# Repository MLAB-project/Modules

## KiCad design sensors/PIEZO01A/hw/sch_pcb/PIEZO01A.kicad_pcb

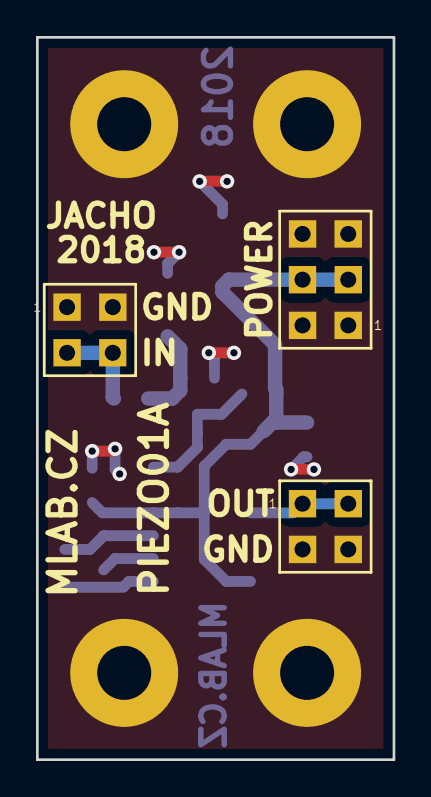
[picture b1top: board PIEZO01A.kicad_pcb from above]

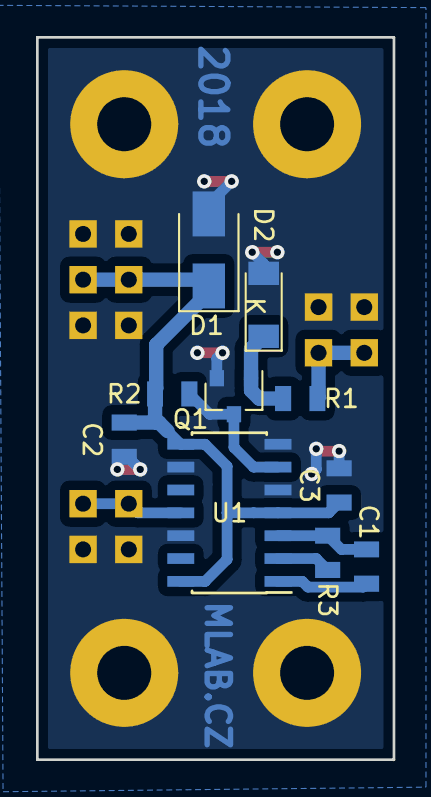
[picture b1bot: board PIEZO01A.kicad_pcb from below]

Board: 2 copper layers, 19.8 x 40.1 mm, 17 parts (10 on the bottom side), 9 nets.

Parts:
C1, C2, C3: 100nF; SMD-0805
D1: M4; Diode-SMA_Standard
D2: 1N4148; Diode-MiniMELF_Standard
J1: 5V; Straight_2x03
J2, J3: HEADER_2x02_PARALLEL; Straight_2x02
M1, M2, M3, M4: HOLE; MountingHole_3mm
Q1: BC817-40; SOT-23
R1: 1k; SMD-0805
R2: 150k; SMD-0805
R3: 10k; SMD-0805
U1: HEF4047BT.652; SOIC-14_3.9x8.7mm_P1.27mm

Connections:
+5V: C2.1, C3.1, D1.1, J1.3, J1.4, R2.2, U1.4, U1.8, U1.14
GND: C2.2, C3.2, D1.2, D2.2, J1.1, J1.2, J1.5, J1.6, J2.1, J2.2, J3.3, J3.4, M1.1, M2.1, M3.1, M4.1, Q1.2, U1.5, U1.7, U1.9, U1.12
unnamed: C1.1, U1.1
unnamed: C1.2, R3.2, U1.3
unnamed: D2.1, Q1.1, R1.1
unnamed: J2.3, J2.4, R1.2
unnamed: J3.1, J3.2, U1.11
unnamed: Q1.3, R2.1, U1.6
unnamed: R3.1, U1.2

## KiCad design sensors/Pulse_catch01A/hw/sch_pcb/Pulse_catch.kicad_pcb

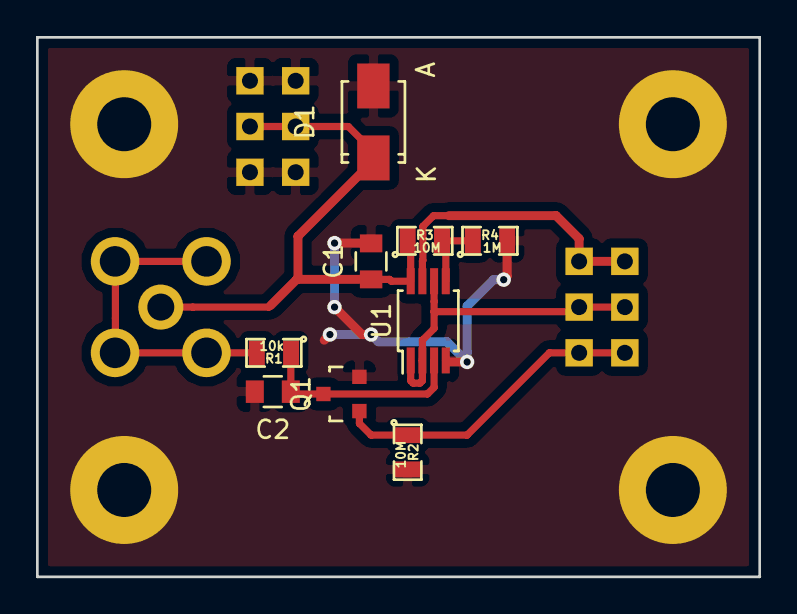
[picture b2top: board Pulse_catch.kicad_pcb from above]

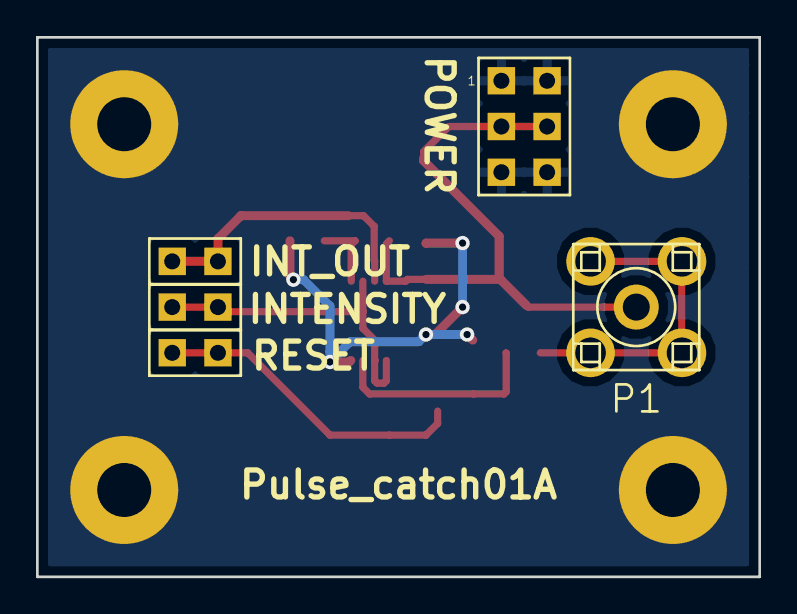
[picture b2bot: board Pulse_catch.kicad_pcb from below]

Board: 2 copper layers, 40.1 x 30.0 mm, 18 parts (5 on the bottom side), 8 nets.

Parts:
C1, C2: 100nF; C_0805
D1: D_Schottky; SMA_Standard
J1: HEADER_2x03_PARALLEL; Straight_2x03
J2: INTENSITY; Straight_2x01
J3: RESET; Straight_2x01
J4: INT_OUT; Straight_2x01
M1, M2, M3, M4: HOLE; MountingHole_3mm
P1: SMA; SMA6251A13G50
Q1: 2N7002; SOT-23
R1: 10k; SMD-0805
R2, R3: 10M; SMD-0805
R4: 1M; SMD-0805
U1: MCP6002; MSOP-8_3x3mm_Pitch0.65mm

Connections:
GNDA: C1.2, C2.2, D1.2, J1.1, J1.2, J1.5, J1.6, M1.1, M2.1, M3.1, M4.1, Q1.2, R2.2, R4.2, U1.4
unnamed: C2.1, Q1.3, R1.1, U1.3
unnamed: J2.1, J2.2, U1.1, U1.2, U1.6
unnamed: J3.1, J3.2, Q1.1, R2.1
unnamed: J4.1, J4.2, U1.7
unnamed: P1.2, R1.2
unnamed: R3.2, R4.1, U1.5
VDD: C1.1, D1.1, J1.3, J1.4, P1.1, R3.1, U1.8

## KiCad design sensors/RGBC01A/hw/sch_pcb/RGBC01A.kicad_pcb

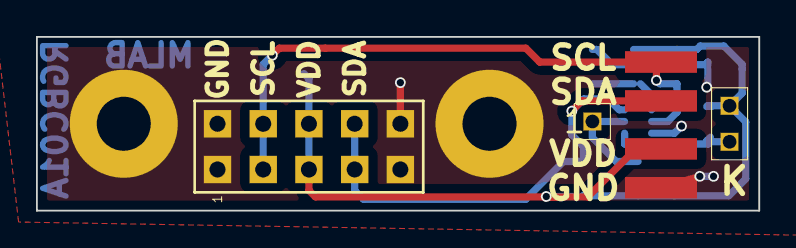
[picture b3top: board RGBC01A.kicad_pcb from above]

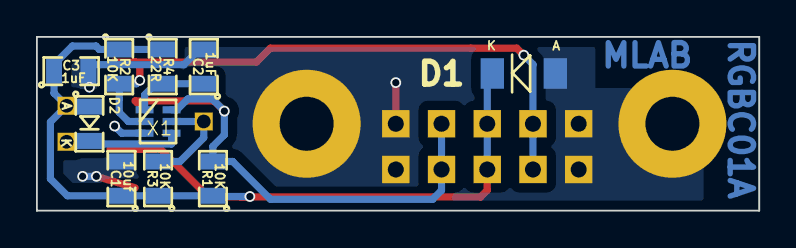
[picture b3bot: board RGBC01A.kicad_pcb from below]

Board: 2 copper layers, 40.1 x 9.7 mm, 19 parts (12 on the bottom side), 7 nets.

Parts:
C1: 10uf; SMD-0805
C2, C3: 1uF; SMD-0805
D1: BZV55C-3,6V; Diode-MiniMELF_Standard
D2: LL-S170IRC-2A; LED_0805
J1: JUMP_5X2; Straight_2x05
J2: CONN1_1; Straight_1x01
J3: CONN1_2; Straight_2x01
J4, J5, J6, J7: CONN1_1; SMD_1x1
M1, M2: HOLE; MountingHole_3mm
R1, R2, R3: 10K; SMD-0805
R4: 22R; SMD-0805
X1: TCS37717; FN

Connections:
/SCL: J1.3, J1.4, J5.1, R2.2, X1.2
/SDA: J1.7, J1.8, J6.1, R1.2, X1.6
GND: C1.2, C2.2, C3.2, D1.1, J1.1, J1.2, J1.9, J1.10, J7.1, M1.1, M2.1, X1.3
unnamed: C2.1, R4.2, X1.1
unnamed: D2.2, J3.2, X1.4
unnamed: J2.1, R3.2, X1.5
VDD: C1.1, C3.1, D1.2, D2.1, J1.5, J1.6, J3.1, J4.1, R1.1, R2.1, R3.1, R4.1

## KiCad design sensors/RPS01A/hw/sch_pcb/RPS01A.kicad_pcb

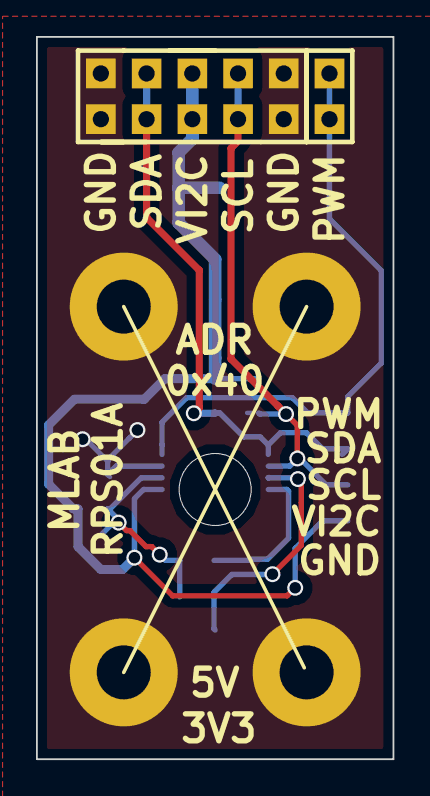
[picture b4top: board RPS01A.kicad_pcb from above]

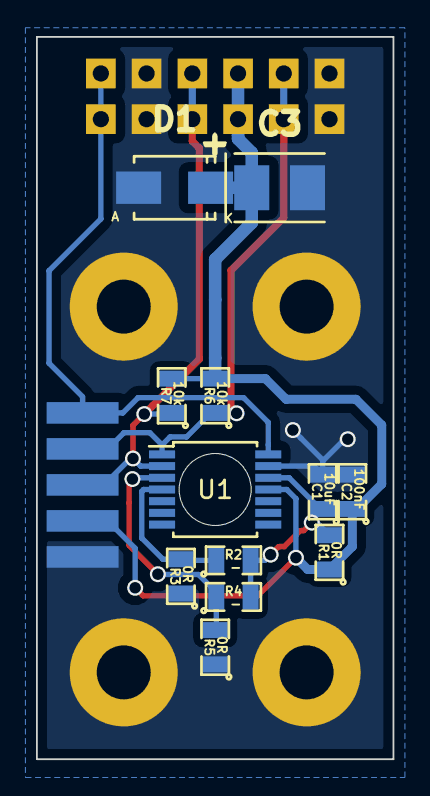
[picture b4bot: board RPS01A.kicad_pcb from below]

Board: 2 copper layers, 19.8 x 40.1 mm, 19 parts (13 on the bottom side), 8 nets.

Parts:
C1: 10uF; SMD-0805
C2: 100nF; SMD-0805
C3: 10uF; TantalC_SizeB_Reflow
D1: M4; SMA_Standard
J1: JUMP_5X2; Pin_Header_Straight_2x05
J2: JUMP_2x1; Pin_Header_Straight_2x01
J3: JUMP_5X2; SMD_JUMP1X5
P1, P2, P3, P4: _; MountingHole_3mm
R1, R3, R5: 0R; SMD-0805
R2, R4: -; SMD-0805
R6, R7: 10k; SMD-0805
U1: AS5048B; TSSOP-14_4.4x5mm_Pitch0.65mm

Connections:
/A1: R2.1, R3.2, U1.4
/A2: R4.1, R5.2, U1.3
/PWM: J2.1, J2.2, J3.5, U1.14
/SCL: J1.2, J1.9, J3.3, R7.1, U1.2
/SDA: J1.4, J1.7, J3.4, R6.1, U1.1
/VDD3V: C1.1, R1.2, R2.2, R4.2, U1.12
GND: C1.2, C2.2, C3.2, D1.1, J1.1, J1.5, J1.6, J1.10, J3.1, P1.1, P2.1, P3.1, P4.1, R3.1, R5.1, U1.13
VDD: C2.1, C3.1, D1.2, J1.3, J1.8, J3.2, R1.1, R6.2, R7.2, U1.11

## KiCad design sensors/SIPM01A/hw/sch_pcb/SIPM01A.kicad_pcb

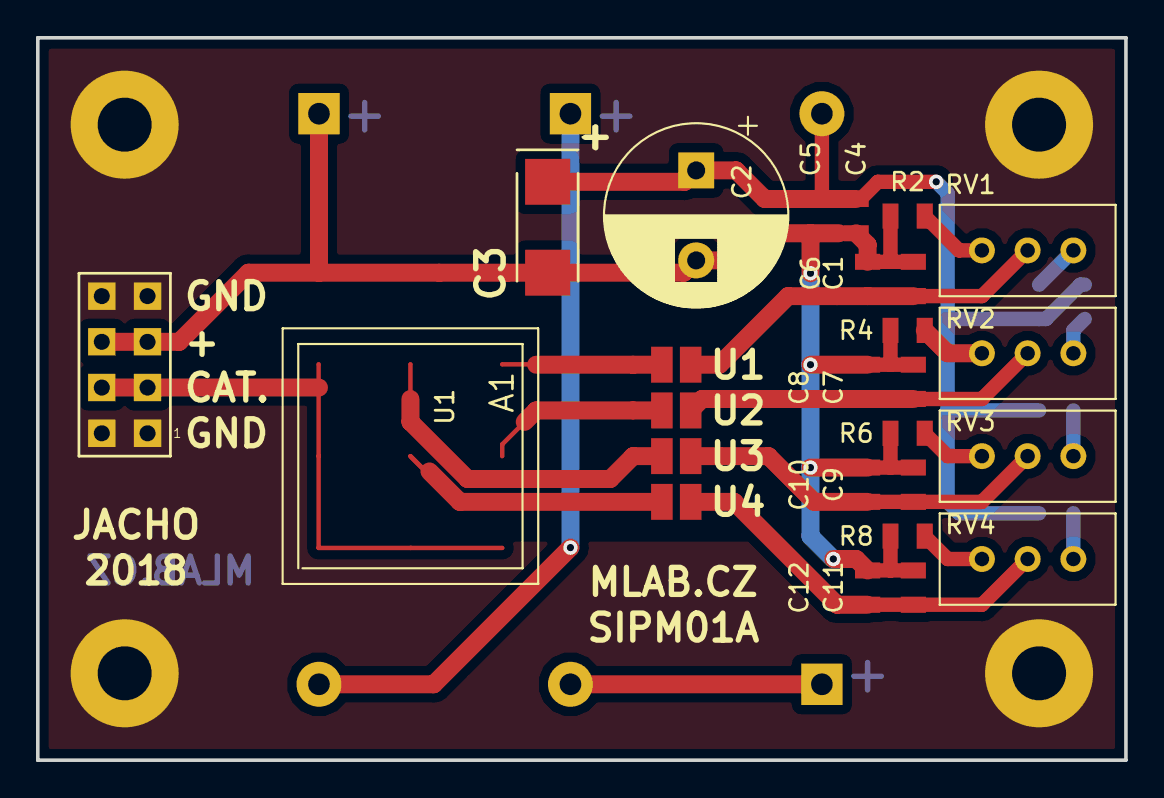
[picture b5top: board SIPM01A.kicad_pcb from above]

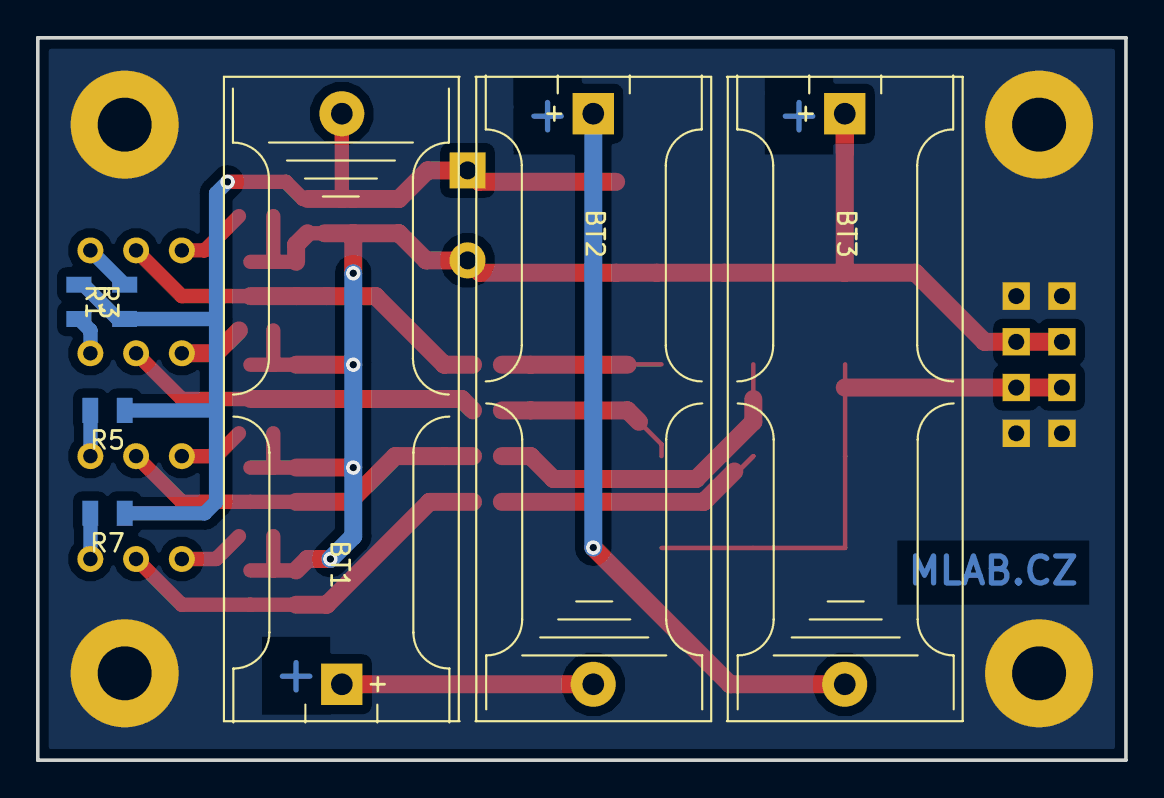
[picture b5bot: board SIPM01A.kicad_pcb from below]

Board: 2 copper layers, 60.5 x 40.1 mm, 37 parts (7 on the bottom side), 22 nets.

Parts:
BT1, BT2, BT3: BH23APC
C1, C4, C7, C9, C11: 4u7/50V; SMD-0805
C2: 470uF/50V - GT470/50; CP_Radial_D10.0mm_P5.00mm
C3: -; TantalC_SizeC_Reflow
C5: 100nF/50V; SMD-0805
C6, C8, C10, C12: 100n/50V; SMD-0805
J1: HEADER_2x04_PARALLEL; Straight_2x04
J2, J3, J4, J5: JUMP2_2x1; Zkrat
M1, M2, M3, M4: HOLE; MountingHole_3mm
R1, R2, R3, R4, R5, R6, R7, R8: R; SMD-0805
RV1, RV2, RV3, RV4: 3296W; Potentiometer_Bourns_3296W_Vertical
U1: ARRAYC-60035-4P-BGA; ArrayC-60035-4P-BGA

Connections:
/U1: C1.1, C6.1, J2.2, RV1.2
/U2: C7.1, C8.1, J3.2, RV2.2
/U3: C9.1, C10.1, J4.2, RV3.2
/U4: C11.1, C12.1, J5.2, RV4.2
GND: J1.1, J1.2, J1.7, J1.8, M1.1, M2.1, M3.1, M4.1
unnamed: BT1.1, BT2.2
unnamed: BT1.2, C2.1, C3.1, C4.1, C5.1, R1.1, R3.1, R5.1, R7.1
unnamed: BT2.1, BT3.2
unnamed: BT3.1, C1.2, C2.2, C3.2, C4.2, C5.2, C6.2, C7.2, C8.2, C9.2, C10.2, C11.2, C12.2, J1.5, J1.6, R2.2, R4.2, R6.2, R8.2
unnamed: J1.3, J1.4, U1.A3, U1.B3, U1.C1, U1.C2, U1.C3
unnamed: J2.1, U1.A1
unnamed: J3.1, U1.A2
unnamed: J4.1, U1.B1
unnamed: J5.1, U1.B2
unnamed: R1.2, RV1.1
unnamed: R2.1, RV1.3
unnamed: R3.2, RV2.1
unnamed: R4.1, RV2.3
unnamed: R5.2, RV3.1
unnamed: R6.1, RV3.3
unnamed: R7.2, RV4.1
unnamed: R8.1, RV4.3

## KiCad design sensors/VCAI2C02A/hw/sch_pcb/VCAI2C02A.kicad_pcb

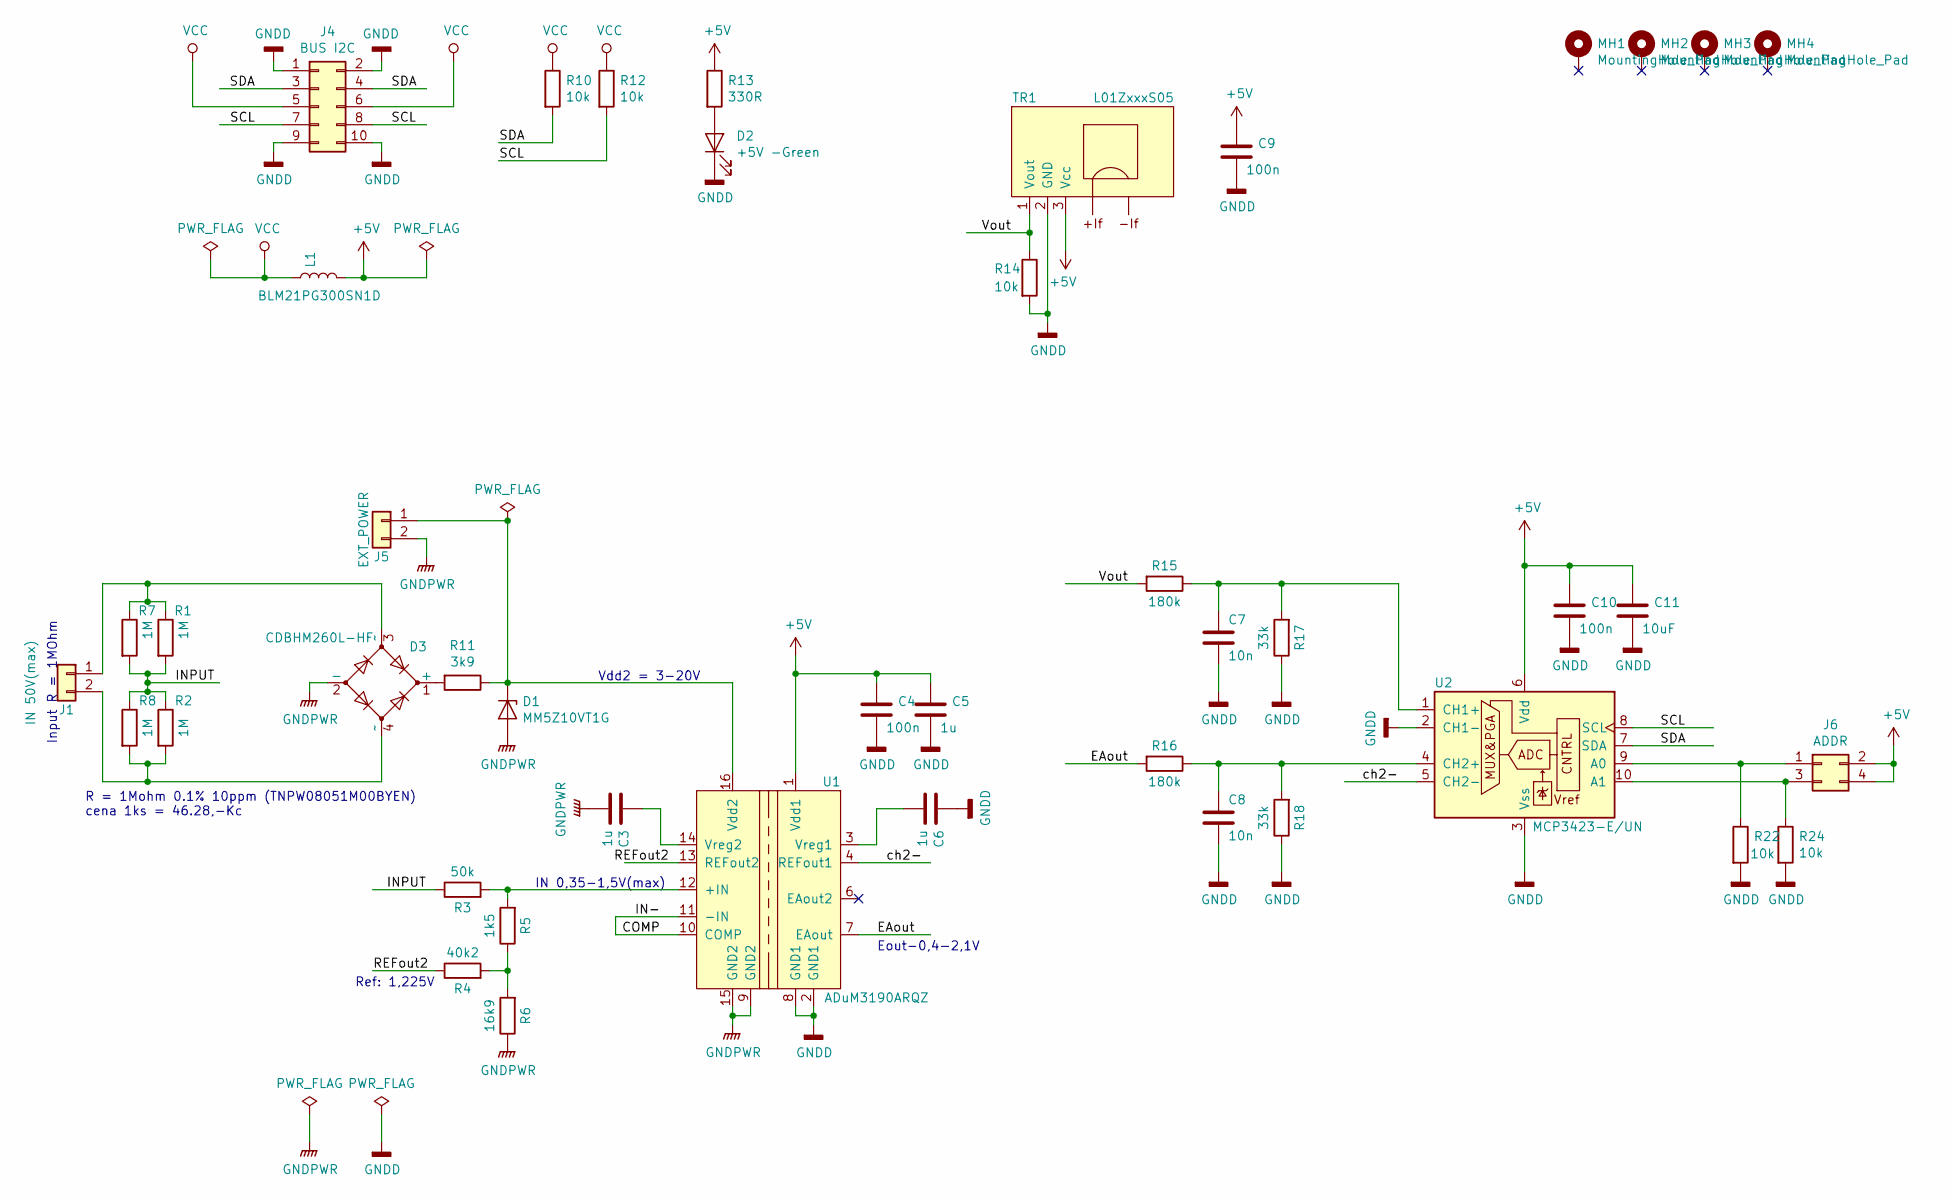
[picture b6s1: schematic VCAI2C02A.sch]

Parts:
C3, C5, C6: 1u; C_0805_2012Metric
C4, C9, C10: 100n; C_0805_2012Metric
C7, C8: 10n; C_0805_2012Metric
C11: 10uF; CP_EIA-3528-21_Kemet-B
D1: MM5Z10VT1G; D_SOD-523
D2: +5V -Green; LED_1206
D3: CDBHM260L-HF; MSB-2
J1: IN 50V(max); XT30PW-M
J4: BUS I2C; Straight_2x05
J5: EXT_POWER; Straight_2x01
J6: ADDR; Straight_2x02
L1: BLM21PG300SN1D; BLM21PG_3Amp
MH1, MH2, MH3, MH4: MountingHole_Pad; MountingHole_3mm
R1, R2, R7, R8: 1M; R_0805_2012Metric
R3: 50k; R_0805_2012Metric
R4: 40k2; R_0805_2012Metric
R5: 1k5; R_0805_2012Metric
R6: 16k9; R_0805_2012Metric
R10, R12, R14, R22, R24: 10k; R_0805_2012Metric
R11: 3k9; R_0805_2012Metric
R13: 330R; R_0805_2012Metric
R15, R16: 180k; R_0805_2012Metric
R17, R18: 33k; R_0805_2012Metric
TR1: L01ZxxxS05
U1: ADuM3190ARQZ; QSOP-16_3.9x4.9mm_P0.635mm
U2: MCP3423-E/UN; MSOP-10_3x3mm_P0.5mm

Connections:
+5V: C4.1, C5.1, C9.1, C10.1, C11.1, J6.2, J6.4, L1.2, R13.1, TR1.3 (Vcc), U1.1 (Vdd1), U2.6 (Vdd)
/COMP: U1.10 (COMP), U1.11 (-IN)
/EAout: R16.2, U1.7 (EAout)
/INPUT: R1.2, R2.1, R3.1, R7.2, R8.1
/REFout2: R4.1, U1.13 (REFout2)
/SCL: J4.7, J4.8, R12.2, U2.8 (SCL)
/SDA: J4.3, J4.4, R10.2, U2.7 (SDA)
/Vout: R14.1, R15.2, TR1.1 (Vout)
/ch2-: U1.4 (REFout1), U2.5 (CH2-)
GNDD: C4.2, C5.2, C6.1, C7.2, C8.2, C9.2, C10.2, C11.2, D2.1 (K), J4.1, J4.2, J4.9, J4.10, R14.2, R17.1, R18.1, R22.2, R24.2, TR1.2 (GND), U1.2 (GND1), U1.8 (GND1), U2.2 (CH1-), U2.3 (Vss)
GNDPWR: C3.2, D1.2 (A), D3.2 (-), J5.2, R6.1, U1.9 (GND2), U1.15 (GND2)
unnamed: C3.1, U1.14 (Vreg2)
unnamed: C6.2, U1.3 (Vreg1)
unnamed: C7.1, R15.1, R17.2, U2.1 (CH1+)
unnamed: C8.1, R16.1, R18.2, U2.4 (CH2+)
unnamed: D1.1 (K), J5.1, R11.1, U1.16 (Vdd2)
unnamed: D2.2 (A), R13.2
unnamed: D3.1 (+), R11.2
unnamed: D3.3 (~~), J1.1, R1.1, R7.1
unnamed: D3.4 (~~), J1.2, R2.2, R8.2
unnamed: J6.1, R22.1, U2.9 (A0)
unnamed: J6.3, R24.1, U2.10 (A1)
unnamed: R3.2, R5.2, U1.12 (+IN)
unnamed: R4.2, R5.1, R6.2
VCC: J4.5, J4.6, L1.1, R10.1, R12.1

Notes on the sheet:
Vdd2 = 3-20V
Input R = 1MOhm
Eout-0,4-2,1V
IN 0,35-1,5V(max)
Ref: 1,225V
R = 1Mohm 0.1% 10ppm (TNPW08051M00BYEN) cena 1ks = 46.28,-Kc

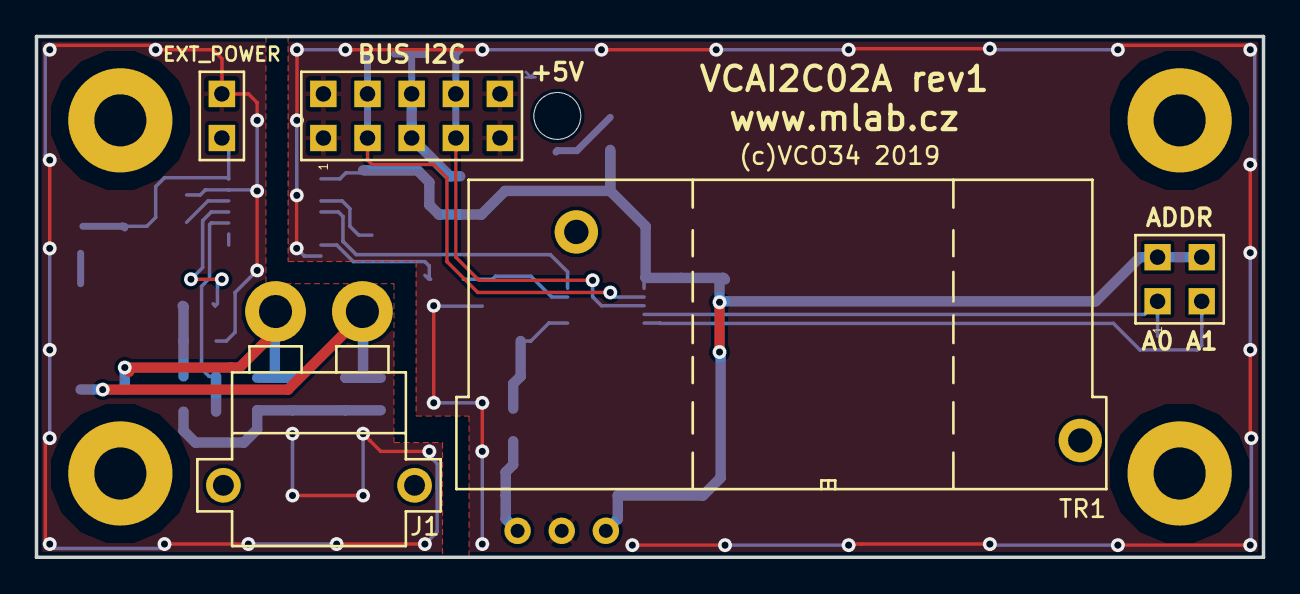
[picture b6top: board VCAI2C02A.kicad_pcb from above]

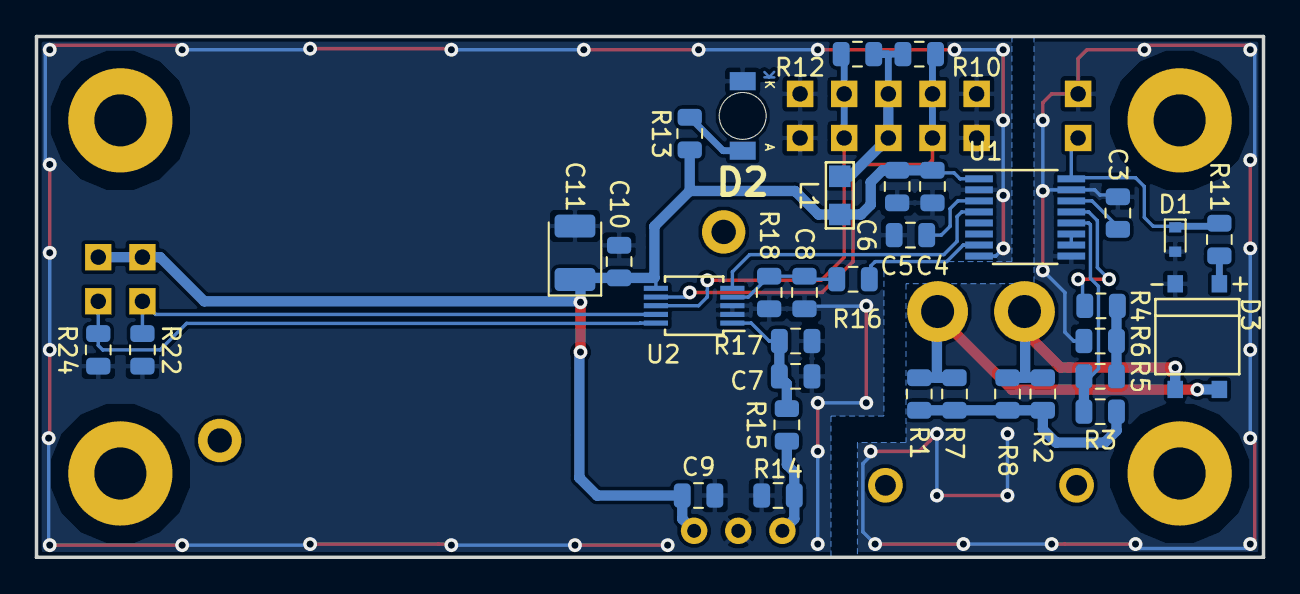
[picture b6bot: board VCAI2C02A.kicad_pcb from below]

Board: 2 copper layers, 70.6 x 30.0 mm, 43 parts (34 on the bottom side), 25 nets.

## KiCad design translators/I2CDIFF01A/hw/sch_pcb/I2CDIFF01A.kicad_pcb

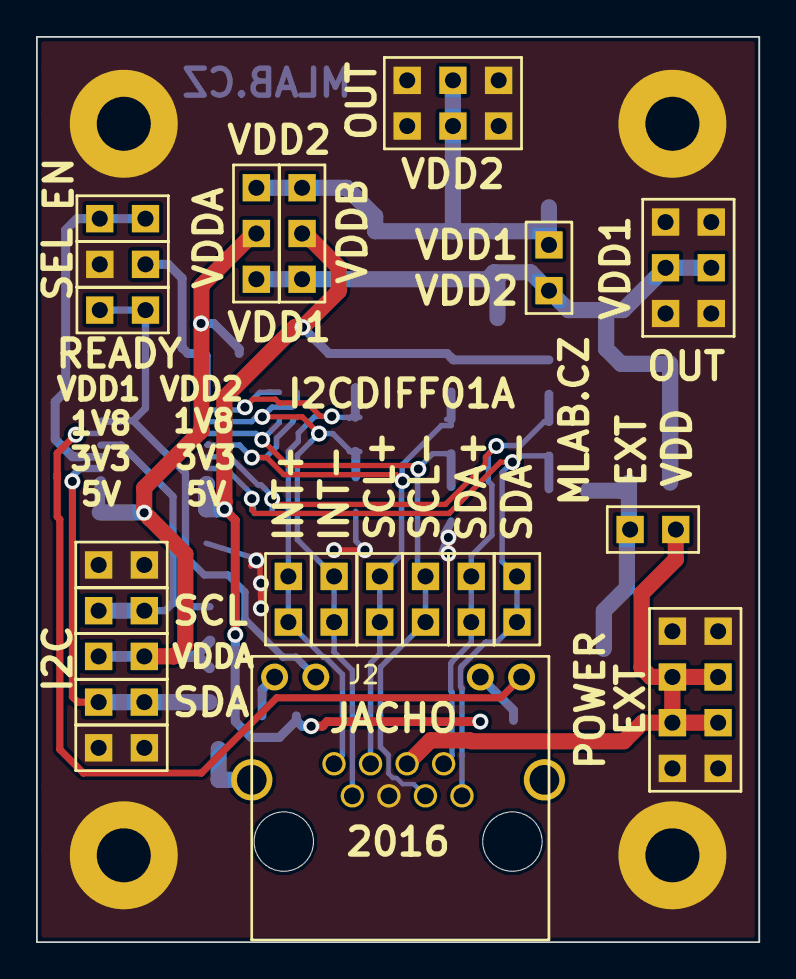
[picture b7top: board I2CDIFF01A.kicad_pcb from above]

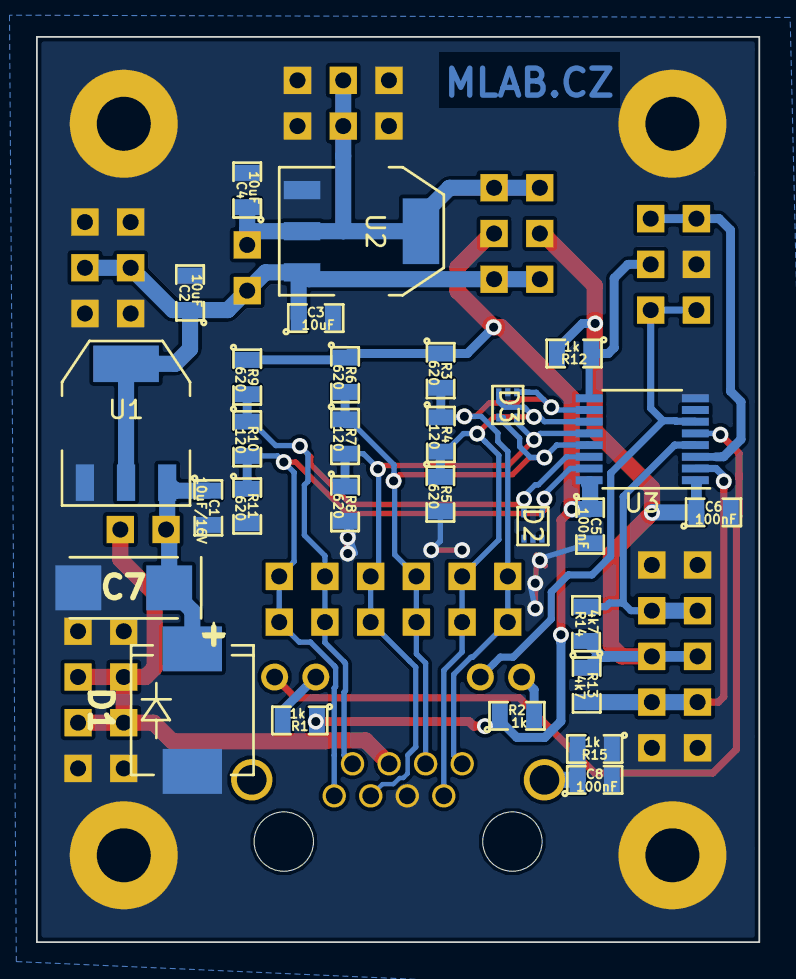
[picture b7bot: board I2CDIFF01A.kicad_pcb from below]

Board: 2 copper layers, 40.1 x 50.3 mm, 55 parts (29 on the bottom side), 22 nets.

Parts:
C1: 10uF/16V; SMD-0805
C2, C3, C4: 10uF; SMD-0805
C5, C6, C8: 100nF; SMD-0805
C7: 47uF; TantalC_SizeC_Reflow
D1: SMBJ15A-E3/52; Diode-SMC_Standard
D2, D3: SP1001-04XTG; SOT-553
J1: JUMP_4X2; Straight_2x04
J2: RJ45_RJHSE-5384; RJHSE-5384(RJ45)
J3, J19, J20, J21, J22, J23: JUMP_2x1; Straight_1x02
J4, J5, J6, J7, J8, J9: JUMP_2x1; Straight_2x01
J10, J13: JUMP_3X2; Straight_2x03
J11, J14, J17: JUMP2_2x1; Straight_2x01
J12, J15: CONN_3; Straight_1x03
J16: EN; Straight_1x02
M1, M2, M3, M4: HOLE; MountingHole_3mm
R1, R2, R12, R15: 1k; SMD-0805
R3, R5, R6, R8, R9, R11: 620; SMD-0805
R4, R7, R10: 120; SMD-0805
R13, R14: 4k7; SMD-0805
U1: LM1117 5V; SOT-223
U2: LM1117 3V3; SOT-223
U3: PCA9616; TSSOP-16_4.4x5mm_Pitch0.65mm

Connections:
/EN: J16.1, J16.2, U3.3
/INT+: D3.1, J2.8, J4.1, J4.2, R3.2, R4.1, U3.10
/INT-: D3.3, J2.7, J5.1, J5.2, R4.2, R5.1, U3.11
/PIDENT: J2.9, U3.5
/READY: J2.11, J3.1, J3.2, U3.6
/SCL+: D3.4, J2.6, J6.1, J6.2, R6.2, R7.1, U3.13
/SCL-: D3.5, J2.3, J7.1, J7.2, R7.2, R8.1, U3.12
/SDA+: D2.5, J2.2, J8.1, J8.2, R9.2, R10.1, U3.14
/SDA-: D2.4, J2.1, J9.1, J9.2, R10.2, R11.1, U3.15
/VDD1: C2.1, C3.1, J10.3, J10.4, J11.2, J12.3, J15.3, U1.2, U1.4, U2.3
/VDD2: C4.1, J11.1, J12.1, J13.3, J13.4, J15.1, U2.2, U2.4
/VddA: C6.1, J15.2, J21.1, J21.2, R12.2, R13.1, R14.1, U3.1
/VddB: C5.1, J12.2, R1.1, R2.1, R3.1, R6.1, R9.1, U3.16
GND: C1.2, C2.2, C3.2, C4.2, C5.2, C6.2, C7.2, C8.2, D1.1, D2.2, D3.2, J1.1, J1.2, J1.7, J1.8, J2.5, J10.1, J10.2, J10.5, J10.6, J13.1, J13.2, J13.5, J13.6, J14.1, J19.1, J19.2, J23.1, J23.2, M1.1, M2.1, M3.1, M4.1, R5.2, R8.2, R11.2, R15.1, U1.1, U2.1, U3.8
unnamed: C8.1, J2.13, R15.2
unnamed: J2.10, R1.2
unnamed: J2.12, R2.2
unnamed: J14.2, R12.1, U3.9
SCL: J22.1, J22.2, R14.2, U3.4
SDA: J20.1, J20.2, R13.2, U3.2
VCC: J1.3, J1.4, J1.5, J1.6, J2.4, J17.2
VDD: C1.1, C7.1, D1.2, J17.1, U1.3
